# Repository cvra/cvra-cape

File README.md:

# CVRA cape

A Beaglebone black extension board for robots used at [CVRA](http://www.cvra.ch/).

## Features
- 2x CAN interfaces with transceivers
    - 1x over native CAN peripheral
    - 1x over CAN-SPI chip
- 16x PWM outputs (using a PCA9685 chip over I2C)
    - 13x to control servo motors
    - 1x to control an RGB LED
- 7x analog inputs with voltage dividers and option to power (3-pin connector)
    - 1x analog Lidar 1D input
    - 1x battery voltage sense
    - 1x CAN-bus voltage sense
    - 4x free
- 18x digital inputs with voltage dividers and option to power (3-pin connector)
- 10x digital outputs (LEDs) with NPN stage to draw 10-100mA
- Power the BBB over the CAN-bus or over USB (switch)
- 1x I2C connector
- 1x UART connector
- 1x RTC with battery soldered directly on the cape

## Notes

### PWM
The PWM outputs are provided by a PWM chip controlled over I2C (PCA9685).

### CAN
There are 2 CAN interfaces on the cape. We use one. The other CAN uses an SPI (TBD).
- `CAN1` uses the `DCAN1` interface on the Beaglebone
    * `CAN1_RX` is on pin `P9.24`
    * `CAN1_TX` is on pin `P9.26`

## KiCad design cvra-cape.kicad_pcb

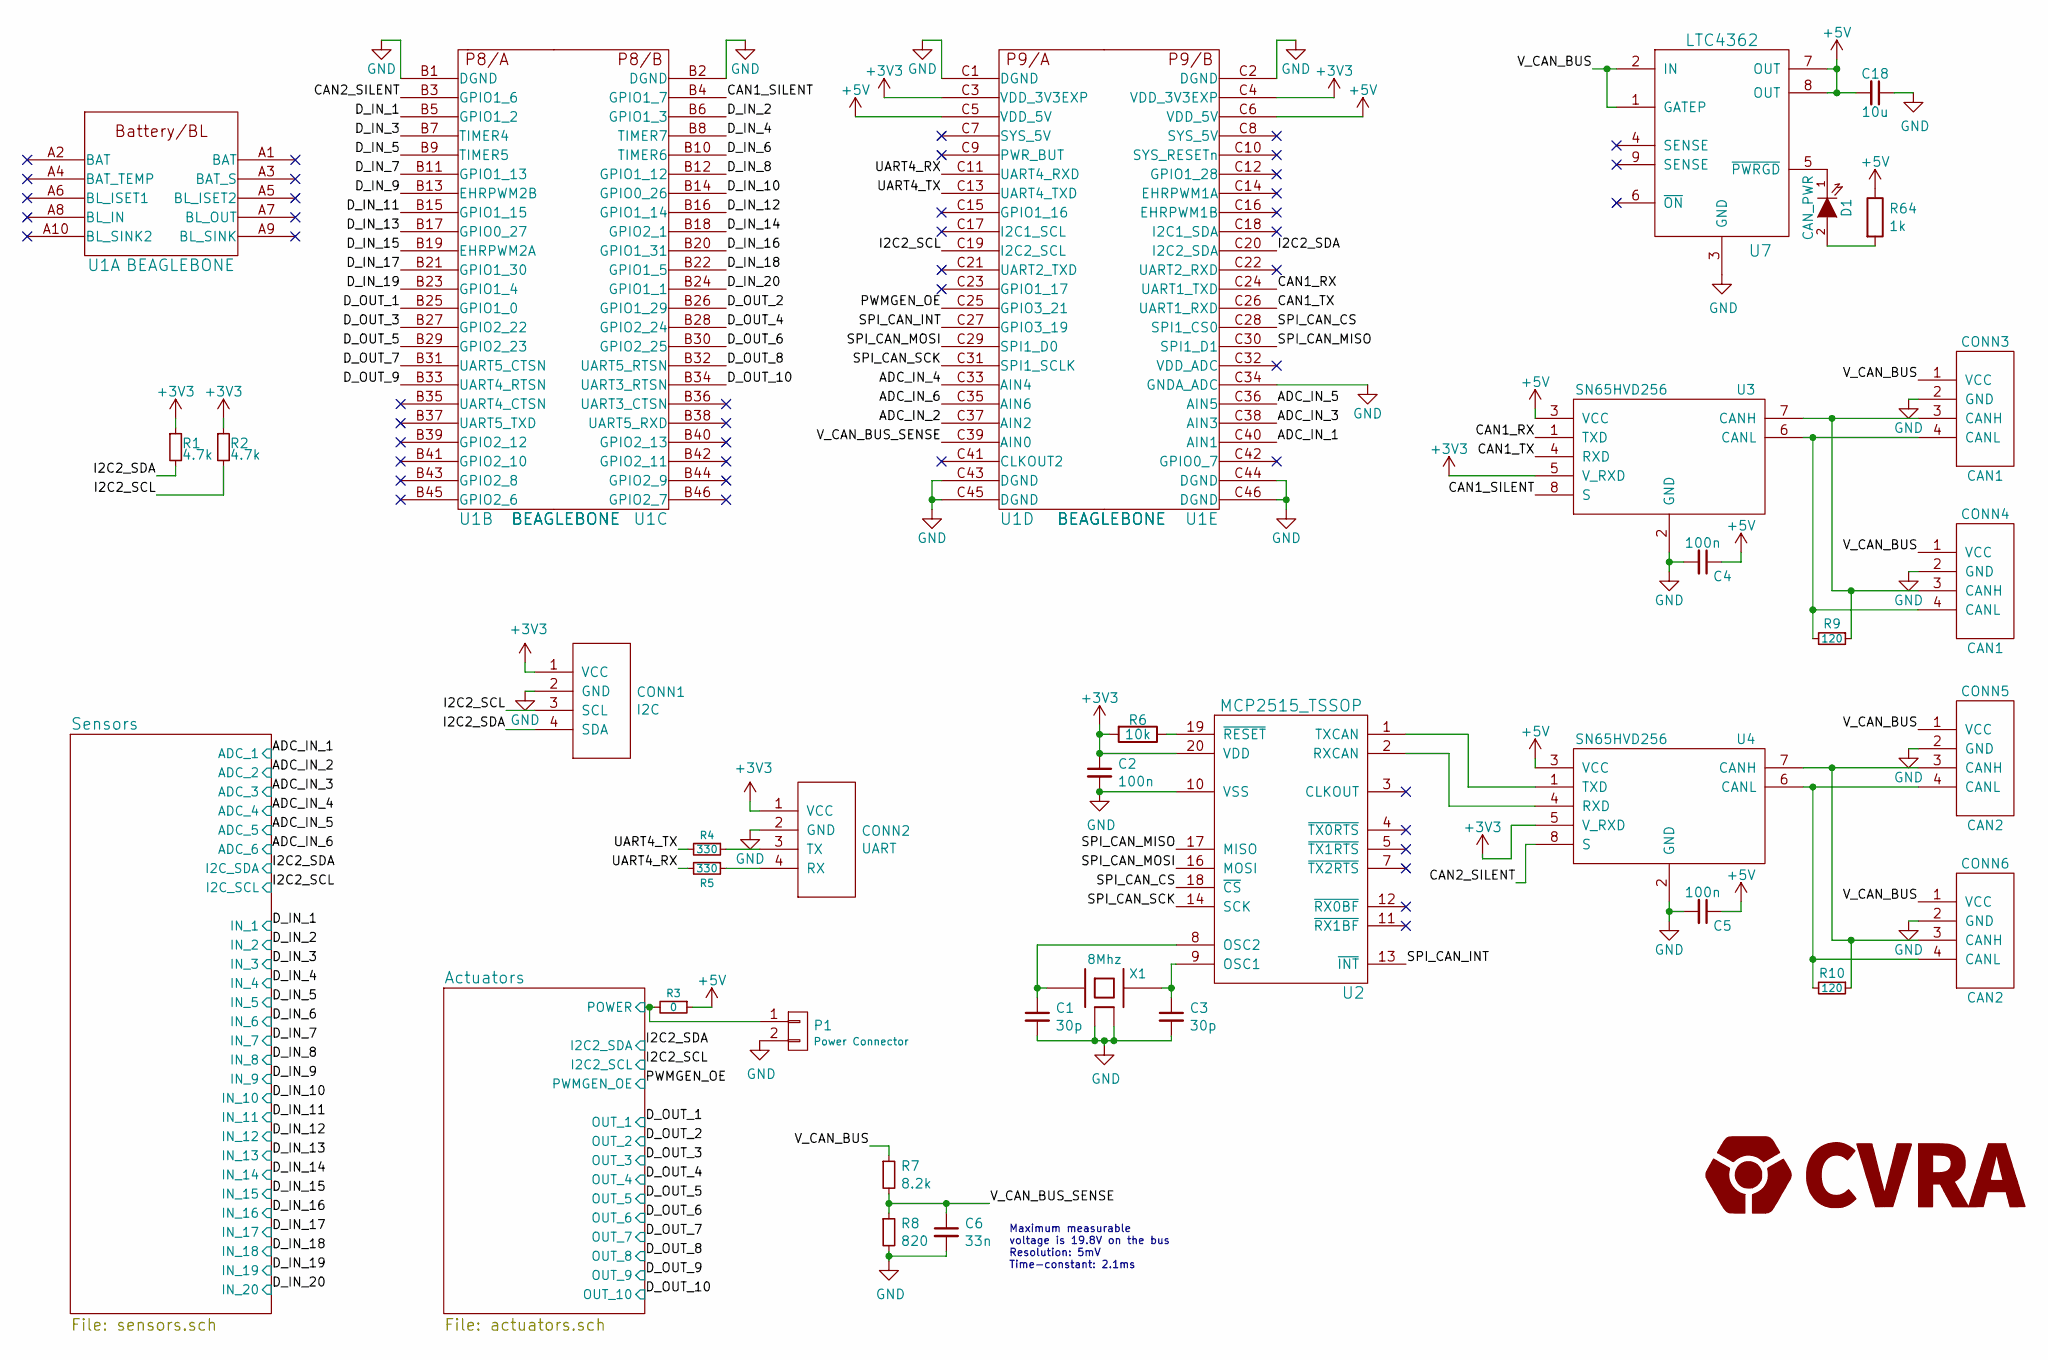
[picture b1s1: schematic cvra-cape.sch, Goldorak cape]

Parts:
C1, C3: 30p; _0603
C2, C4, C5: 100n; _0603
C6: 33n; _0603
C18: 10u; _0603
CONN1: I2C; _Molex-PicoBlade-SMD-4
CONN2: UART; _Molex-PicoBlade-SMD-4
CONN3, CONN4: CAN1; _Molex-PicoBlade-SMD-4
CONN5, CONN6: CAN2; _Molex-PicoBlade-SMD-4
D1: CAN_PWR; _0603
P1: Power Connector; Pin_Header_Straight_1x02
R1, R2: 4.7k; _0603
R3: 0; _0603
R4, R5: 330; _0603
R6: 10k; _0603
R7: 8.2k; _0603
R8: 820; _0603
R9, R10: 120; _0603
R64: 1k; _0603
U1: BEAGLEBONE
U2: MCP2515_TSSOP; TSSOP-20_4.4x6.5mm_Pitch0.65mm
U3, U4: SN65HVD256; _SO-8
U7: LTC4362; DFN_8-Lead_2mmx3mm
X1: 8Mhz; XTAL_ABMM2

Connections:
+3V3: C2.1, CONN1.1 (VCC), CONN2.1 (VCC), R1.1, R2.1, R6.2, U1.C3 (VDD_3V3EXP), U1.C4 (VDD_3V3EXP), U2.20 (VDD), U3.5 (V_RXD), U4.5 (V_RXD); also elsewhere on the board
+5V: C4.1, C5.1, C18.2, R3.1, R64.1, U1.C5 (VDD_5V), U1.C6 (VDD_5V), U3.3 (VCC), U4.3 (VCC), U7.7 (OUT), U7.8 (OUT)
/ADC_IN_1: U1.C40 (AIN1); also elsewhere on the board
/ADC_IN_2: U1.C37 (AIN2); also elsewhere on the board
/ADC_IN_3: U1.C38 (AIN3); also elsewhere on the board
/ADC_IN_4: U1.C33 (AIN4); also elsewhere on the board
/ADC_IN_5: U1.C36 (AIN5); also elsewhere on the board
/ADC_IN_6: U1.C35 (AIN6); also elsewhere on the board
/Actuators/POWER: P1.1, R3.2; also elsewhere on the board
/CAN1_RX: U1.C24 (UART1_TXD), U3.1 (TXD)
/CAN1_SILENT: U1.B4 (GPIO1_7), U3.8 (S)
/CAN1_TX: U1.C26 (UART1_RXD), U3.4 (RXD)
/CAN2_SILENT: U1.B3 (GPIO1_6), U4.8 (S)
/D_IN_1: U1.B5 (GPIO1_2); also elsewhere on the board
/D_IN_2: U1.B6 (GPIO1_3); also elsewhere on the board
/D_IN_3: U1.B7 (TIMER4); also elsewhere on the board
/D_IN_4: U1.B8 (TIMER7); also elsewhere on the board
/D_IN_5: U1.B9 (TIMER5); also elsewhere on the board
/D_IN_6: U1.B10 (TIMER6); also elsewhere on the board
/D_IN_7: U1.B11 (GPIO1_13); also elsewhere on the board
/D_IN_8: U1.B12 (GPIO1_12); also elsewhere on the board
/D_IN_9: U1.B13 (EHRPWM2B); also elsewhere on the board
/D_IN_10: U1.B14 (GPIO0_26); also elsewhere on the board
/D_IN_11: U1.B15 (GPIO1_15); also elsewhere on the board
/D_IN_12: U1.B16 (GPIO1_14); also elsewhere on the board
/D_IN_13: U1.B17 (GPIO0_27); also elsewhere on the board
/D_IN_14: U1.B18 (GPIO2_1); also elsewhere on the board
/D_IN_15: U1.B19 (EHRPWM2A); also elsewhere on the board
/D_IN_16: U1.B20 (GPIO1_31); also elsewhere on the board
/D_IN_17: U1.B21 (GPIO1_30); also elsewhere on the board
/D_IN_18: U1.B22 (GPIO1_5); also elsewhere on the board
/D_IN_19: U1.B23 (GPIO1_4); also elsewhere on the board
/D_IN_20: U1.B24 (GPIO1_1); also elsewhere on the board
/D_OUT_1: U1.B25 (GPIO1_0); also elsewhere on the board
/D_OUT_2: U1.B26 (GPIO1_29); also elsewhere on the board
/D_OUT_3: U1.B27 (GPIO2_22); also elsewhere on the board
/D_OUT_4: U1.B28 (GPIO2_24); also elsewhere on the board
/D_OUT_5: U1.B29 (GPIO2_23); also elsewhere on the board
/D_OUT_6: U1.B30 (GPIO2_25); also elsewhere on the board
/D_OUT_7: U1.B31 (UART5_CTSN); also elsewhere on the board
/D_OUT_8: U1.B32 (UART5_RTSN); also elsewhere on the board
/D_OUT_9: U1.B33 (UART4_RTSN); also elsewhere on the board
/D_OUT_10: U1.B34 (UART3_RTSN); also elsewhere on the board
/I2C2_SCL: CONN1.3 (SCL), R2.2, U1.C19 (I2C2_SCL); also elsewhere on the board
/I2C2_SDA: CONN1.4 (SDA), R1.2, U1.C20 (I2C2_SDA); also elsewhere on the board
/PWMGEN_OE: U1.C25 (GPIO3_21); also elsewhere on the board
/SPI_CAN_CS: U1.C28 (SPI1_CS0), U2.18 (~CS)
/SPI_CAN_INT: U1.C27 (GPIO3_19), U2.13 (~INT)
/SPI_CAN_MISO: U1.C30 (SPI1_D1), U2.17 (MISO)
/SPI_CAN_MOSI: U1.C29 (SPI1_D0), U2.16 (MOSI)
/SPI_CAN_SCK: U1.C31 (SPI1_SCLK), U2.14 (SCK)
/UART4_RX: R5.2, U1.C11 (UART4_RXD)
/UART4_TX: R4.2, U1.C13 (UART4_TXD)
/V_CAN_BUS: CONN3.1 (VCC), CONN4.1 (VCC), CONN5.1 (VCC), CONN6.1 (VCC), R7.1, U7.1 (GATEP), U7.2 (IN)
/V_CAN_BUS_SENSE: C6.1, R7.2, R8.1, U1.C39 (AIN0)
GND: C1.2, C2.2, C3.2, C4.2, C5.2, C6.2, C18.1, CONN1.2 (GND), CONN1.MECH (GND), CONN2.2 (GND), CONN2.MECH (GND), CONN3.2 (GND), CONN3.MECH (GND), CONN4.2 (GND), CONN4.MECH (GND), CONN5.2 (GND), CONN5.MECH (GND), CONN6.2 (GND), CONN6.MECH (GND), P1.2, R8.2, U1.B1 (DGND), U1.B2 (DGND), U1.C1 (DGND), U1.C2 (DGND), U1.C34 (GNDA_ADC), U1.C43 (DGND), U1.C44 (DGND), U1.C45 (DGND), U1.C46 (DGND), U2.10 (VSS), U3.2 (GND), U4.2 (GND), U7.3 (GND), X1.2 (case), X1.4 (case); also elsewhere on the board
unnamed: C1.1, U2.8 (OSC2), X1.1
unnamed: C3.1, U2.9 (OSC1), X1.3
unnamed: CONN2.3 (TX), R4.1
unnamed: CONN2.4 (RX), R5.1
unnamed: CONN3.3 (CANH), CONN4.3 (CANH), R9.1, U3.7 (CANH)
unnamed: CONN3.4 (CANL), CONN4.4 (CANL), R9.2, U3.6 (CANL)
unnamed: CONN5.3 (CANH), CONN6.3 (CANH), R10.1, U4.7 (CANH)
unnamed: CONN5.4 (CANL), CONN6.4 (CANL), R10.2, U4.6 (CANL)
unnamed: D1.1 (K), U7.5 (~PWRGD)
unnamed: D1.2 (A), R64.2
unnamed: R6.1, U2.19 (~RESET)
unnamed: U2.1 (TXCAN), U4.1 (TXD)
unnamed: U2.2 (RXCAN), U4.4 (RXD)

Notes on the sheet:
Maximum measurable voltage is 19.8V on the bus Resolution: 5mV Time-constant: 2.1ms

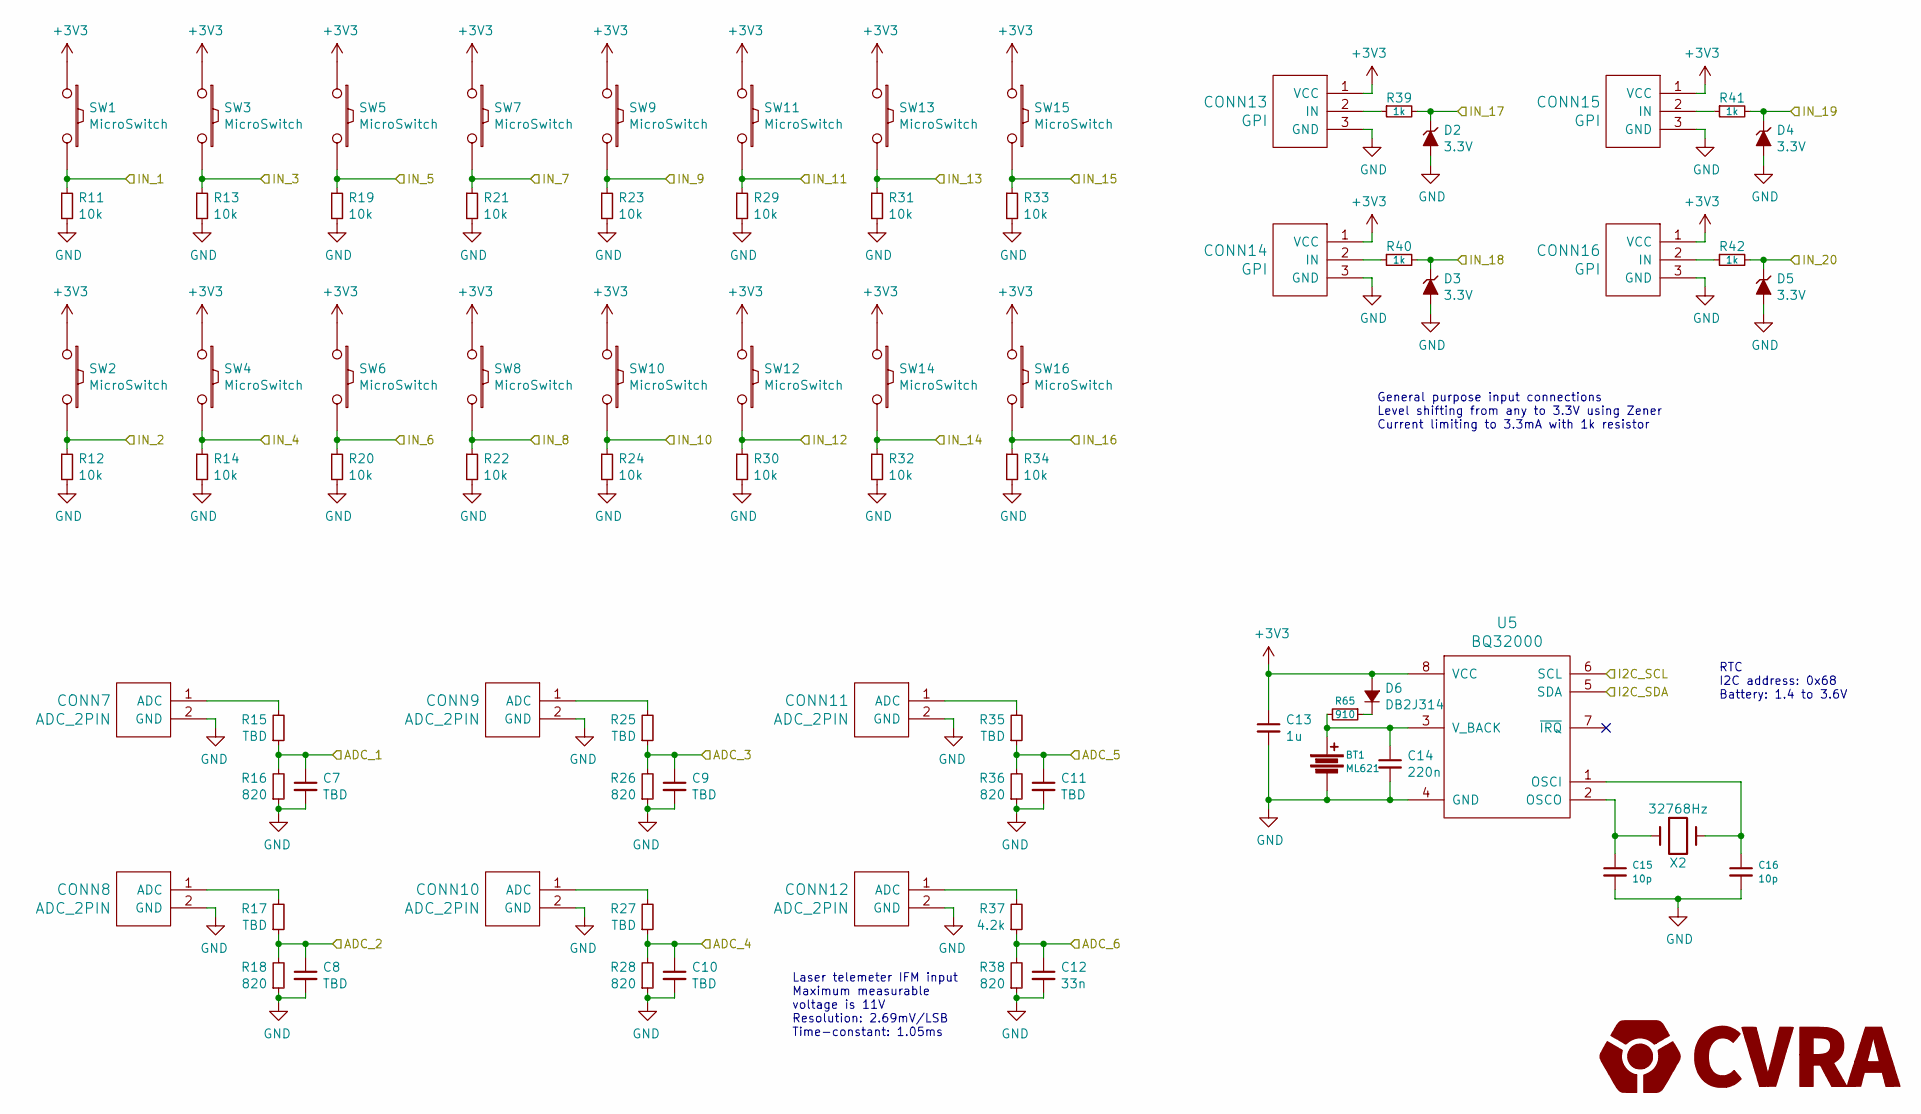
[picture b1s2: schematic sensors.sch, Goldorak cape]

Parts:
BT1: ML621; Battery_ML621
C7, C8, C9, C10, C11: TBD; _0603
C12: 33n; _0603
C13: 1u; _0603
C14: 220n; _0603
C15, C16: 10p; _0603
CONN7, CONN8, CONN9, CONN10, CONN11, CONN12: ADC_2PIN; _Pin2mm_2
CONN13, CONN14, CONN15, CONN16: GPI; _Pin2mm_3
D2, D3, D4, D5: 3.3V; _0603
D6: DB2J314; Diode_SMini2
R11, R12, R13, R14, R19, R20, R21, R22, R23, R24, R29, R30, R31, R32, R33, R34: 10k; _0603
R15, R17, R25, R27, R35: TBD; _0603
R16, R18, R26, R28, R36, R38: 820; _0603
R37: 4.2k; _0603
R39, R40, R41, R42: 1k; _0603
R65: 910; _0603
SW1, SW2, SW3, SW4, SW5, SW6, SW7, SW8, SW9, SW10, SW11, SW12, SW13, SW14, SW15, SW16: MicroSwitch; _Pin2mm_2
U5: BQ32000; _SO-8
X2: 32768Hz; XTAL_ABS07

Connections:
+3V3: C13.1, CONN13.1 (VCC), CONN14.1 (VCC), CONN15.1 (VCC), CONN16.1 (VCC), D6.2 (A), SW1.1, SW2.1, SW3.1, SW4.1, SW5.1, SW6.1, SW7.1, SW8.1, SW9.1, SW10.1, SW11.1, SW12.1, SW13.1, SW14.1, SW15.1, SW16.1, U5.8 (VCC); also elsewhere on the board
/ADC_IN_1: C7.1, R15.1, R16.2; also elsewhere on the board
/ADC_IN_2: C8.1, R17.1, R18.2; also elsewhere on the board
/ADC_IN_3: C9.1, R25.1, R26.2; also elsewhere on the board
/ADC_IN_4: C10.1, R27.1, R28.2; also elsewhere on the board
/ADC_IN_5: C11.1, R35.1, R36.2; also elsewhere on the board
/ADC_IN_6: C12.1, R37.1, R38.2; also elsewhere on the board
/D_IN_1: R11.1, SW1.2; also elsewhere on the board
/D_IN_2: R12.1, SW2.2; also elsewhere on the board
/D_IN_3: R13.1, SW3.2; also elsewhere on the board
/D_IN_4: R14.1, SW4.2; also elsewhere on the board
/D_IN_5: R19.1, SW5.2; also elsewhere on the board
/D_IN_6: R20.1, SW6.2; also elsewhere on the board
/D_IN_7: R21.1, SW7.2; also elsewhere on the board
/D_IN_8: R22.1, SW8.2; also elsewhere on the board
/D_IN_9: R23.1, SW9.2; also elsewhere on the board
/D_IN_10: R24.1, SW10.2; also elsewhere on the board
/D_IN_11: R29.1, SW11.2; also elsewhere on the board
/D_IN_12: R30.1, SW12.2; also elsewhere on the board
/D_IN_13: R31.1, SW13.2; also elsewhere on the board
/D_IN_14: R32.1, SW14.2; also elsewhere on the board
/D_IN_15: R33.1, SW15.2; also elsewhere on the board
/D_IN_16: R34.1, SW16.2; also elsewhere on the board
/D_IN_17: D2.1 (K), R39.2; also elsewhere on the board
/D_IN_18: D3.1 (K), R40.2; also elsewhere on the board
/D_IN_19: D4.1 (K), R41.2; also elsewhere on the board
/D_IN_20: D5.1 (K), R42.2; also elsewhere on the board
/I2C2_SCL: U5.6 (SCL); also elsewhere on the board
/I2C2_SDA: U5.5 (SDA); also elsewhere on the board
GND: BT1.2, C7.2, C8.2, C9.2, C10.2, C11.2, C12.2, C13.2, C14.2, C15.2, C16.2, CONN7.2 (GND), CONN8.2 (GND), CONN9.2 (GND), CONN10.2 (GND), CONN11.2 (GND), CONN12.2 (GND), CONN13.3 (GND), CONN14.3 (GND), CONN15.3 (GND), CONN16.3 (GND), D2.2 (A), D3.2 (A), D4.2 (A), D5.2 (A), R11.2, R12.2, R13.2, R14.2, R16.1, R18.1, R19.2, R20.2, R21.2, R22.2, R23.2, R24.2, R26.1, R28.1, R29.2, R30.2, R31.2, R32.2, R33.2, R34.2, R36.1, R38.1, U5.4 (GND); also elsewhere on the board
unnamed: BT1.1, C14.1, R65.2, U5.3 (V_BACK)
unnamed: C15.1, U5.2 (OSCO), X2.1
unnamed: C16.1, U5.1 (OSCI), X2.2
unnamed: CONN7.1 (ADC), R15.2
unnamed: CONN8.1 (ADC), R17.2
unnamed: CONN9.1 (ADC), R25.2
unnamed: CONN10.1 (ADC), R27.2
unnamed: CONN11.1 (ADC), R35.2
unnamed: CONN12.1 (ADC), R37.2
unnamed: CONN13.2 (IN), R39.1
unnamed: CONN14.2 (IN), R40.1
unnamed: CONN15.2 (IN), R41.1
unnamed: CONN16.2 (IN), R42.1
unnamed: D6.1 (K), R65.1

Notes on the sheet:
RTC I2C address: 0x68 Battery: 1.4 to 3.6V
Laser telemeter IFM input Maximum measurable voltage is 11V Resolution: 2.69mV/LSB Time-constant: 1.05ms
General purpose input connections Level shifting from any to 3.3V using Zener Current limiting to 3.3mA with 1k resistor

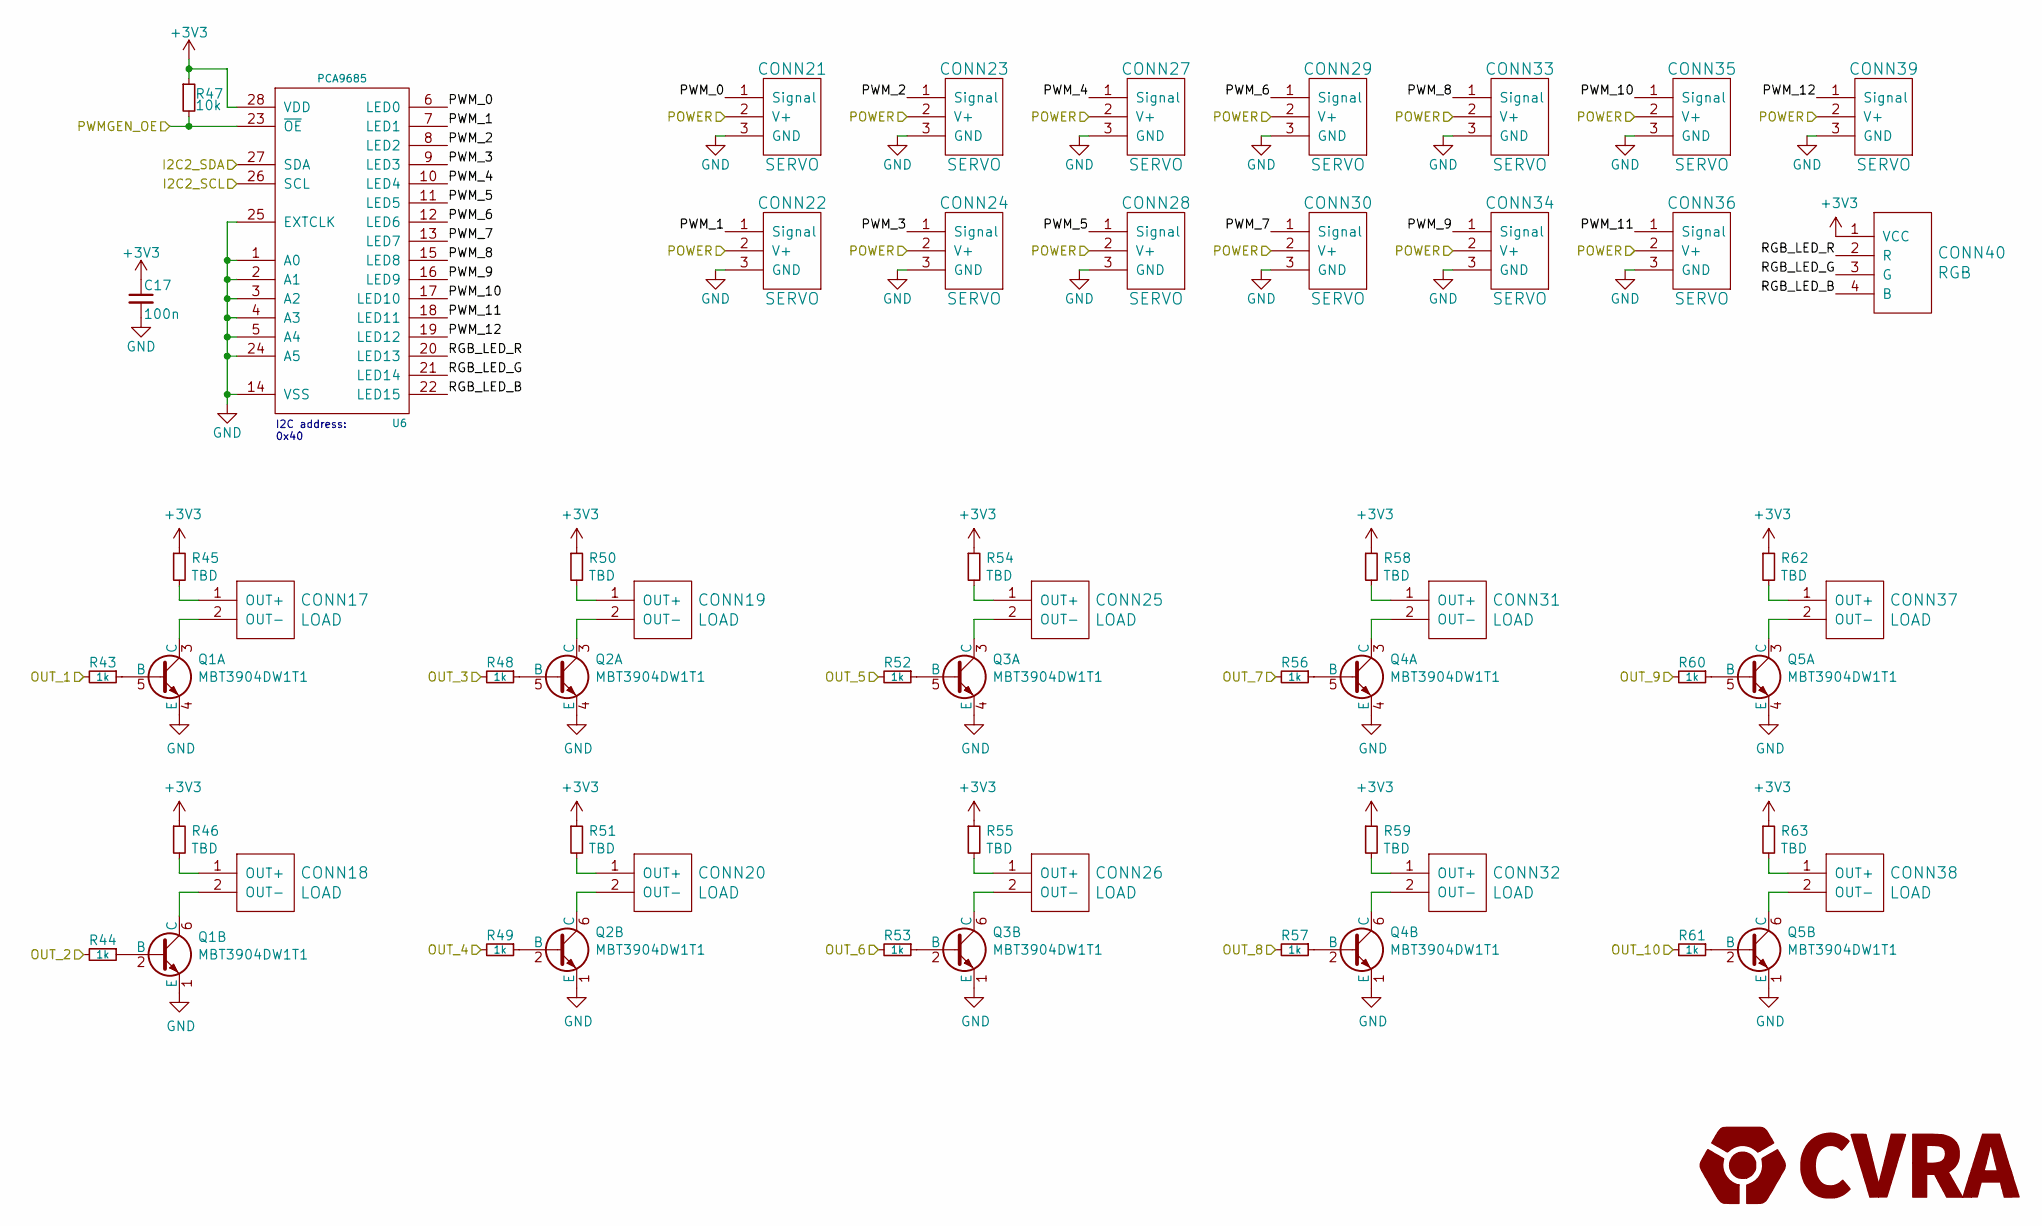
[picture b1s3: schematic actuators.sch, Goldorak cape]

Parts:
C17: 100n; _0603
CONN17, CONN18, CONN19, CONN20, CONN25, CONN26, CONN31, CONN32, CONN37, CONN38: LOAD; _Pin2mm_2
CONN21, CONN22, CONN23, CONN24, CONN27, CONN28, CONN29, CONN30, CONN33, CONN34, CONN35, CONN36, CONN39: SERVO; Pin_Header_Straight_1x03
CONN40: RGB; _Pin2mm_4
Q1, Q2, Q3, Q4, Q5: MBT3904DW1T1; SOT363
R43, R44, R48, R49, R52, R53, R56, R57, R60, R61: 1k; _0603
R45, R46, R50, R51, R54, R55, R58, R59, R62, R63: TBD; _0603
R47: 10k; _0603
U6: PCA9685; TSSOP-28_4.4x9.7mm_Pitch0.65mm

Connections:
+3V3: C17.1, CONN40.1 (VCC), R45.1, R46.1, R47.1, R50.1, R51.1, R54.1, R55.1, R58.1, R59.1, R62.1, R63.1, U6.28 (VDD); also elsewhere on the board
/Actuators/PWM_0: CONN21.1 (Signal), U6.6 (LED0); also elsewhere on the board
/Actuators/PWM_1: CONN22.1 (Signal), U6.7 (LED1); also elsewhere on the board
/Actuators/PWM_2: CONN23.1 (Signal), U6.8 (LED2); also elsewhere on the board
/Actuators/PWM_3: CONN24.1 (Signal), U6.9 (LED3); also elsewhere on the board
/Actuators/PWM_4: CONN27.1 (Signal), U6.10 (LED4); also elsewhere on the board
/Actuators/PWM_5: CONN28.1 (Signal), U6.11 (LED5); also elsewhere on the board
/Actuators/PWM_6: CONN29.1 (Signal), U6.12 (LED6); also elsewhere on the board
/Actuators/PWM_7: CONN30.1 (Signal), U6.13 (LED7); also elsewhere on the board
/Actuators/PWM_8: CONN33.1 (Signal), U6.15 (LED8); also elsewhere on the board
/Actuators/PWM_9: CONN34.1 (Signal), U6.16 (LED9); also elsewhere on the board
/Actuators/PWM_10: CONN35.1 (Signal), U6.17 (LED10); also elsewhere on the board
/Actuators/PWM_11: CONN36.1 (Signal), U6.18 (LED11); also elsewhere on the board
/Actuators/PWM_12: CONN39.1 (Signal), U6.19 (LED12); also elsewhere on the board
/Actuators/RGB_LED_B: CONN40.4 (B), U6.22 (LED15)
/Actuators/RGB_LED_G: CONN40.3 (G), U6.21 (LED14)
/Actuators/RGB_LED_R: CONN40.2 (R), U6.20 (LED13)
/D_OUT_1: R43.2; also elsewhere on the board
/D_OUT_2: R44.2; also elsewhere on the board
/D_OUT_3: R48.2; also elsewhere on the board
/D_OUT_4: R49.2; also elsewhere on the board
/D_OUT_5: R52.2; also elsewhere on the board
/D_OUT_6: R53.2; also elsewhere on the board
/D_OUT_7: R56.2; also elsewhere on the board
/D_OUT_8: R57.2; also elsewhere on the board
/D_OUT_9: R60.2; also elsewhere on the board
/D_OUT_10: R61.2; also elsewhere on the board
/I2C2_SCL: U6.26 (SCL); also elsewhere on the board
/I2C2_SDA: U6.27 (SDA); also elsewhere on the board
/PWMGEN_OE: R47.2, U6.23 (~OE); also elsewhere on the board
GND: C17.2, CONN21.3 (GND), CONN22.3 (GND), CONN23.3 (GND), CONN24.3 (GND), CONN27.3 (GND), CONN28.3 (GND), CONN29.3 (GND), CONN30.3 (GND), CONN33.3 (GND), CONN34.3 (GND), CONN35.3 (GND), CONN36.3 (GND), CONN39.3 (GND), Q1.1 (E), Q1.4 (E), Q2.1 (E), Q2.4 (E), Q3.1 (E), Q3.4 (E), Q4.1 (E), Q4.4 (E), Q5.1 (E), Q5.4 (E), U6.1 (A0), U6.2 (A1), U6.3 (A2), U6.4 (A3), U6.5 (A4), U6.14 (VSS), U6.24 (A5), U6.25 (EXTCLK); also elsewhere on the board
unnamed: CONN17.1 (OUT+), R45.2
unnamed: CONN17.2 (OUT-), Q1.3 (C)
unnamed: CONN18.1 (OUT+), R46.2
unnamed: CONN18.2 (OUT-), Q1.6 (C)
unnamed: CONN19.1 (OUT+), R50.2
unnamed: CONN19.2 (OUT-), Q2.3 (C)
unnamed: CONN20.1 (OUT+), R51.2
unnamed: CONN20.2 (OUT-), Q2.6 (C)
unnamed: CONN21.2 (V+), CONN22.2 (V+), CONN23.2 (V+), CONN24.2 (V+), CONN27.2 (V+), CONN28.2 (V+), CONN29.2 (V+), CONN30.2 (V+), CONN33.2 (V+), CONN34.2 (V+), CONN35.2 (V+), CONN36.2 (V+), CONN39.2 (V+)
unnamed: CONN25.1 (OUT+), R54.2
unnamed: CONN25.2 (OUT-), Q3.3 (C)
unnamed: CONN26.1 (OUT+), R55.2
unnamed: CONN26.2 (OUT-), Q3.6 (C)
unnamed: CONN31.1 (OUT+), R58.2
unnamed: CONN31.2 (OUT-), Q4.3 (C)
unnamed: CONN32.1 (OUT+), R59.2
unnamed: CONN32.2 (OUT-), Q4.6 (C)
unnamed: CONN37.1 (OUT+), R62.2
unnamed: CONN37.2 (OUT-), Q5.3 (C)
unnamed: CONN38.1 (OUT+), R63.2
unnamed: CONN38.2 (OUT-), Q5.6 (C)
unnamed: Q1.2 (B), R44.1
unnamed: Q1.5 (B), R43.1
unnamed: Q2.2 (B), R49.1
unnamed: Q2.5 (B), R48.1
unnamed: Q3.2 (B), R53.1
unnamed: Q3.5 (B), R52.1
unnamed: Q4.2 (B), R57.1
unnamed: Q4.5 (B), R56.1
unnamed: Q5.2 (B), R61.1
unnamed: Q5.5 (B), R60.1

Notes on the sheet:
I2C address: 0x40

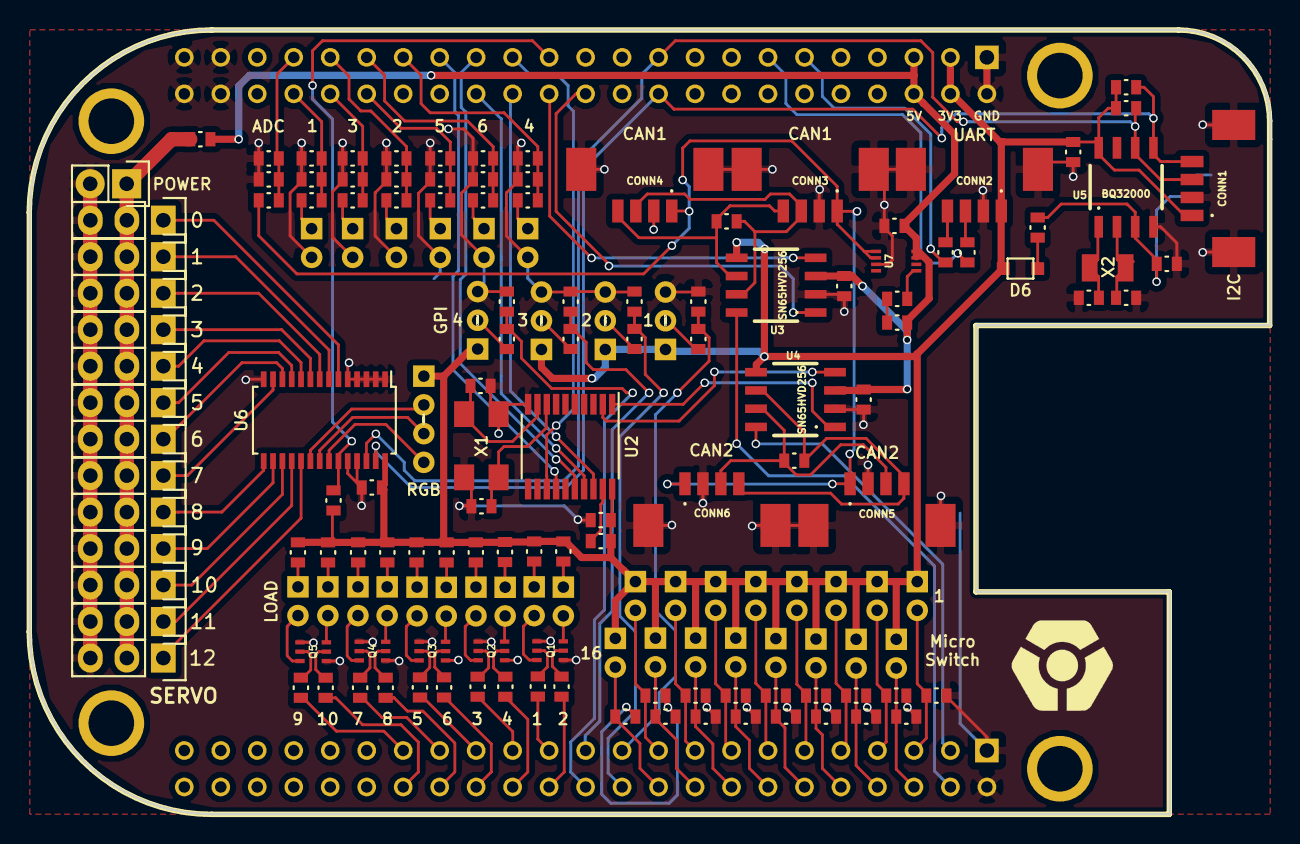
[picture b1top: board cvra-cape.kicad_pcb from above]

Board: 2 copper layers, 86.4 x 54.6 mm, 161 parts (1 on the bottom side), 129 nets.

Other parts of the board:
0, 1, 2, 3, 4, 5, 6, 7, 8, 9, 10, 11, 12: SERVO; Pin_Header_Straight_1x03
POWER: Power Connector; Pin_Header_Straight_1x02

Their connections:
/Actuators/POWER: 0.2, 1.2, 2.2, 3.2, 4.2, 5.2, 6.2, 7.2, 8.2, 9.2, 10.2, 11.2, 12.2, POWER.1; also elsewhere on the board
/Actuators/PWM_0: 0.1; also elsewhere on the board
/Actuators/PWM_1: 1.1; also elsewhere on the board
/Actuators/PWM_2: 2.1; also elsewhere on the board
/Actuators/PWM_3: 3.1; also elsewhere on the board
/Actuators/PWM_4: 4.1; also elsewhere on the board
/Actuators/PWM_5: 5.1; also elsewhere on the board
/Actuators/PWM_6: 6.1; also elsewhere on the board
/Actuators/PWM_7: 7.1; also elsewhere on the board
/Actuators/PWM_8: 8.1; also elsewhere on the board
/Actuators/PWM_9: 9.1; also elsewhere on the board
/Actuators/PWM_10: 10.1; also elsewhere on the board
/Actuators/PWM_11: 11.1; also elsewhere on the board
/Actuators/PWM_12: 12.1; also elsewhere on the board
GND: 0.3, 1.3, 2.3, 3.3, 4.3, 5.3, 6.3, 7.3, 8.3, 9.3, 10.3, 11.3, 12.3, POWER.2; also elsewhere on the board

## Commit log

2015-10-28 Add kicad library as submodule
2015-10-28 Setup KiCad project with libraries & readme
2015-10-28 Add Beaglebone cape component
2015-10-28 Add PWM outputs
2015-10-28 Document PWM output pins numbering
2015-10-28 Add CAN interfaces
2015-10-28 Add BBB header table
2015-10-28 Add components datasheets
    CAN transceiver
    Load switch of CAN bus power
2015-10-28 Add note about CAN interfaces wiring
2015-12-10 Update specs
2015-12-13 Add PWM chip and servo outputs
2015-12-22 Add power from CAN bus and switch to hierarchical labelling
2016-01-20 Add ADC outputs with voltage dividers
2016-02-01 Add CAN over SPI interface using MCP251
2016-02-05 Use 3pin connectors for ADC (with power pin)
2016-02-05 Add RTC
2016-02-08 Add digital inputs with power option
2016-02-08 Add digital outputs with NPN stage
2016-02-08 Annotate
2016-02-08 Generate pdf
2016-02-09 Add decoupling capacitors at ADC inputs
2016-02-12 Add connector for RGB LED
2016-02-12 Correct digital outputs as we want to drive loads (LEDs)
2016-02-14 Wire inputs from switches correctly
2016-02-14 Fix small details & replot pdf
2016-02-20 Correct schematic after review by @vieillemaison
2016-02-21 Update CAN power protection
    Avoid dropout below 5V by using LTC4362 instead of custom protection with Shottky + Fuse
    The chip provides overcurrent and overvoltage protection
2016-02-27 Add a recharge circuit for the RTC backup battery
2016-02-27 Add CVRA logo to schematic
2016-02-27 Associate footprints
2016-02-28 Place components on PCB
2016-02-29 Routing
2016-02-29 Show PCB preview in readme
2016-03-03 Routing corrections
    - Use GND plane on both sides
    - Route power lines as 0.5mm thickness tracks
    - Cleanup crystals wiring (symetry)
    - Cleanup ADC wiring to avoid crosstalk
2016-03-04 Add Power connector for servos and silkscreen annotations
2016-03-04 Generate gerber files
2016-03-10 Final gerber & schematic
2016-03-14 rewrite gerber from kicad OS X
2016-04-07 Final gerbers
